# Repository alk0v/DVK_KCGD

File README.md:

This project is a replica of a color graphic display controller (KCGD) for a DVK computer, reproduced in full accordance with the schematic diagram. Unfortunately, I lost the latest version of the project in KiCAD along with the SSD disk, so the repository contains only what I managed to restore from the backup (about 50% of the finished project). However, the Gerber files were saved.
The boards have been ordered, and one board has been assembled, but unfortunately, there is no way to check its operation. The DVK computer is currently unavailable due to the war in Ukraine.

Цей проект - репліка контролера кольорового графічного дисплею (КЦГД) для комп'ютера ДВК, відтворена у повній відповідності до принципової схеми. На жаль, останню версію проекту в KiCAD я втратив разом з SSD диском, то ж в репозиторії лише те, що вдалося відновити з бекапа (десь 50% готового проекту). Але  зберіглися gerber-файли.
Плати були замовлені, одна плата зібрана, але перевірити її роботу, на жаль, нема можливості. Комп'ютер ДВК зараз недоступний через війну.

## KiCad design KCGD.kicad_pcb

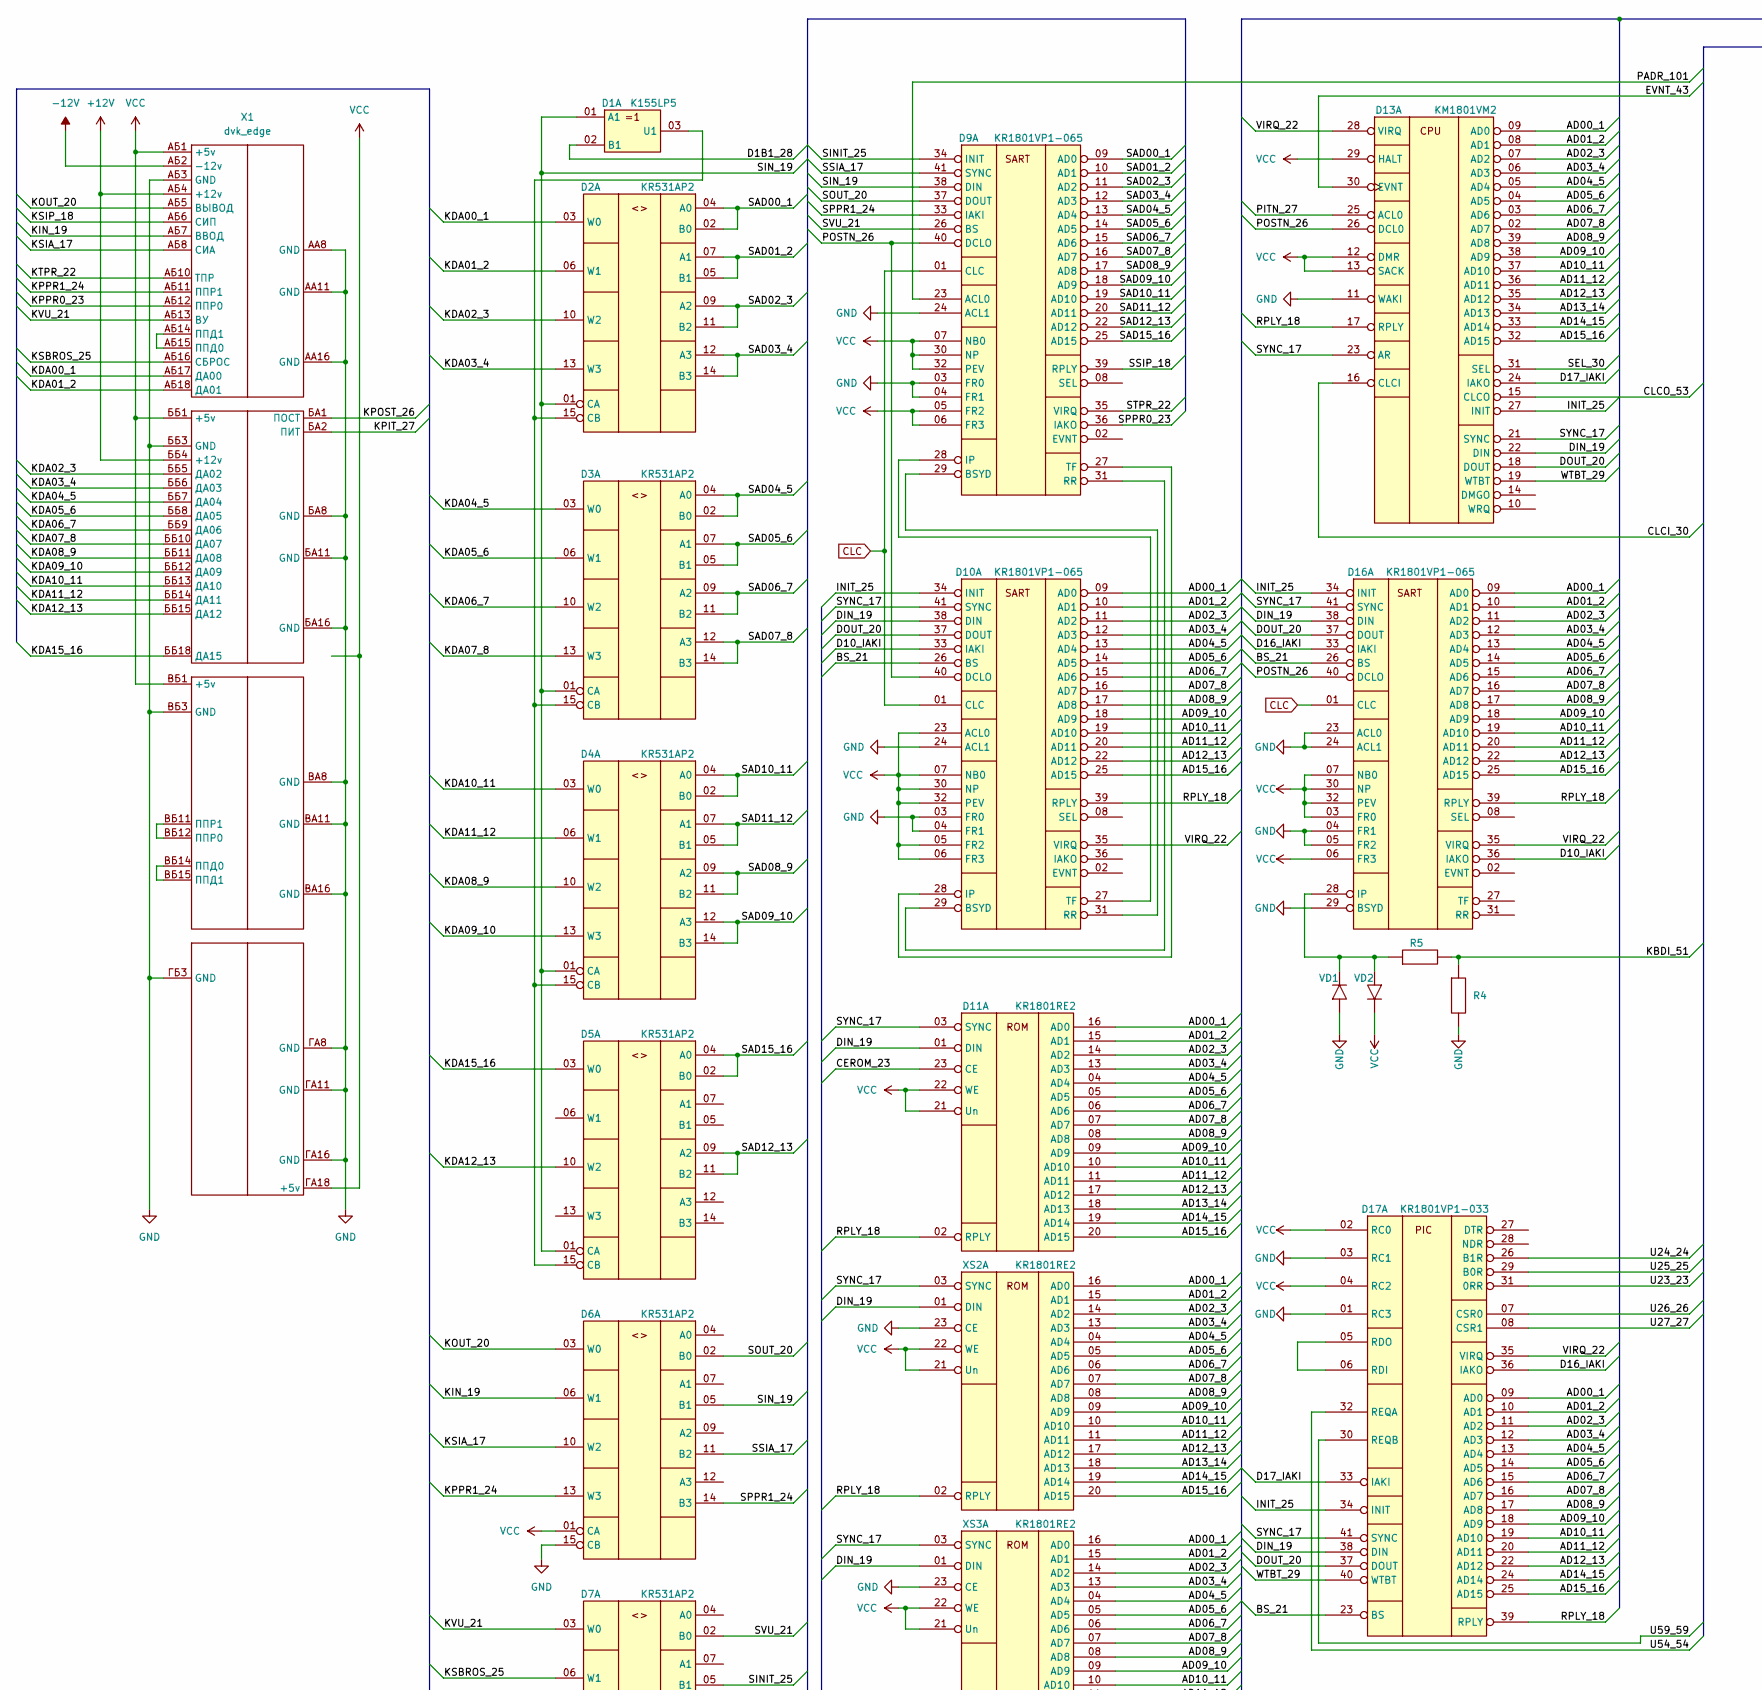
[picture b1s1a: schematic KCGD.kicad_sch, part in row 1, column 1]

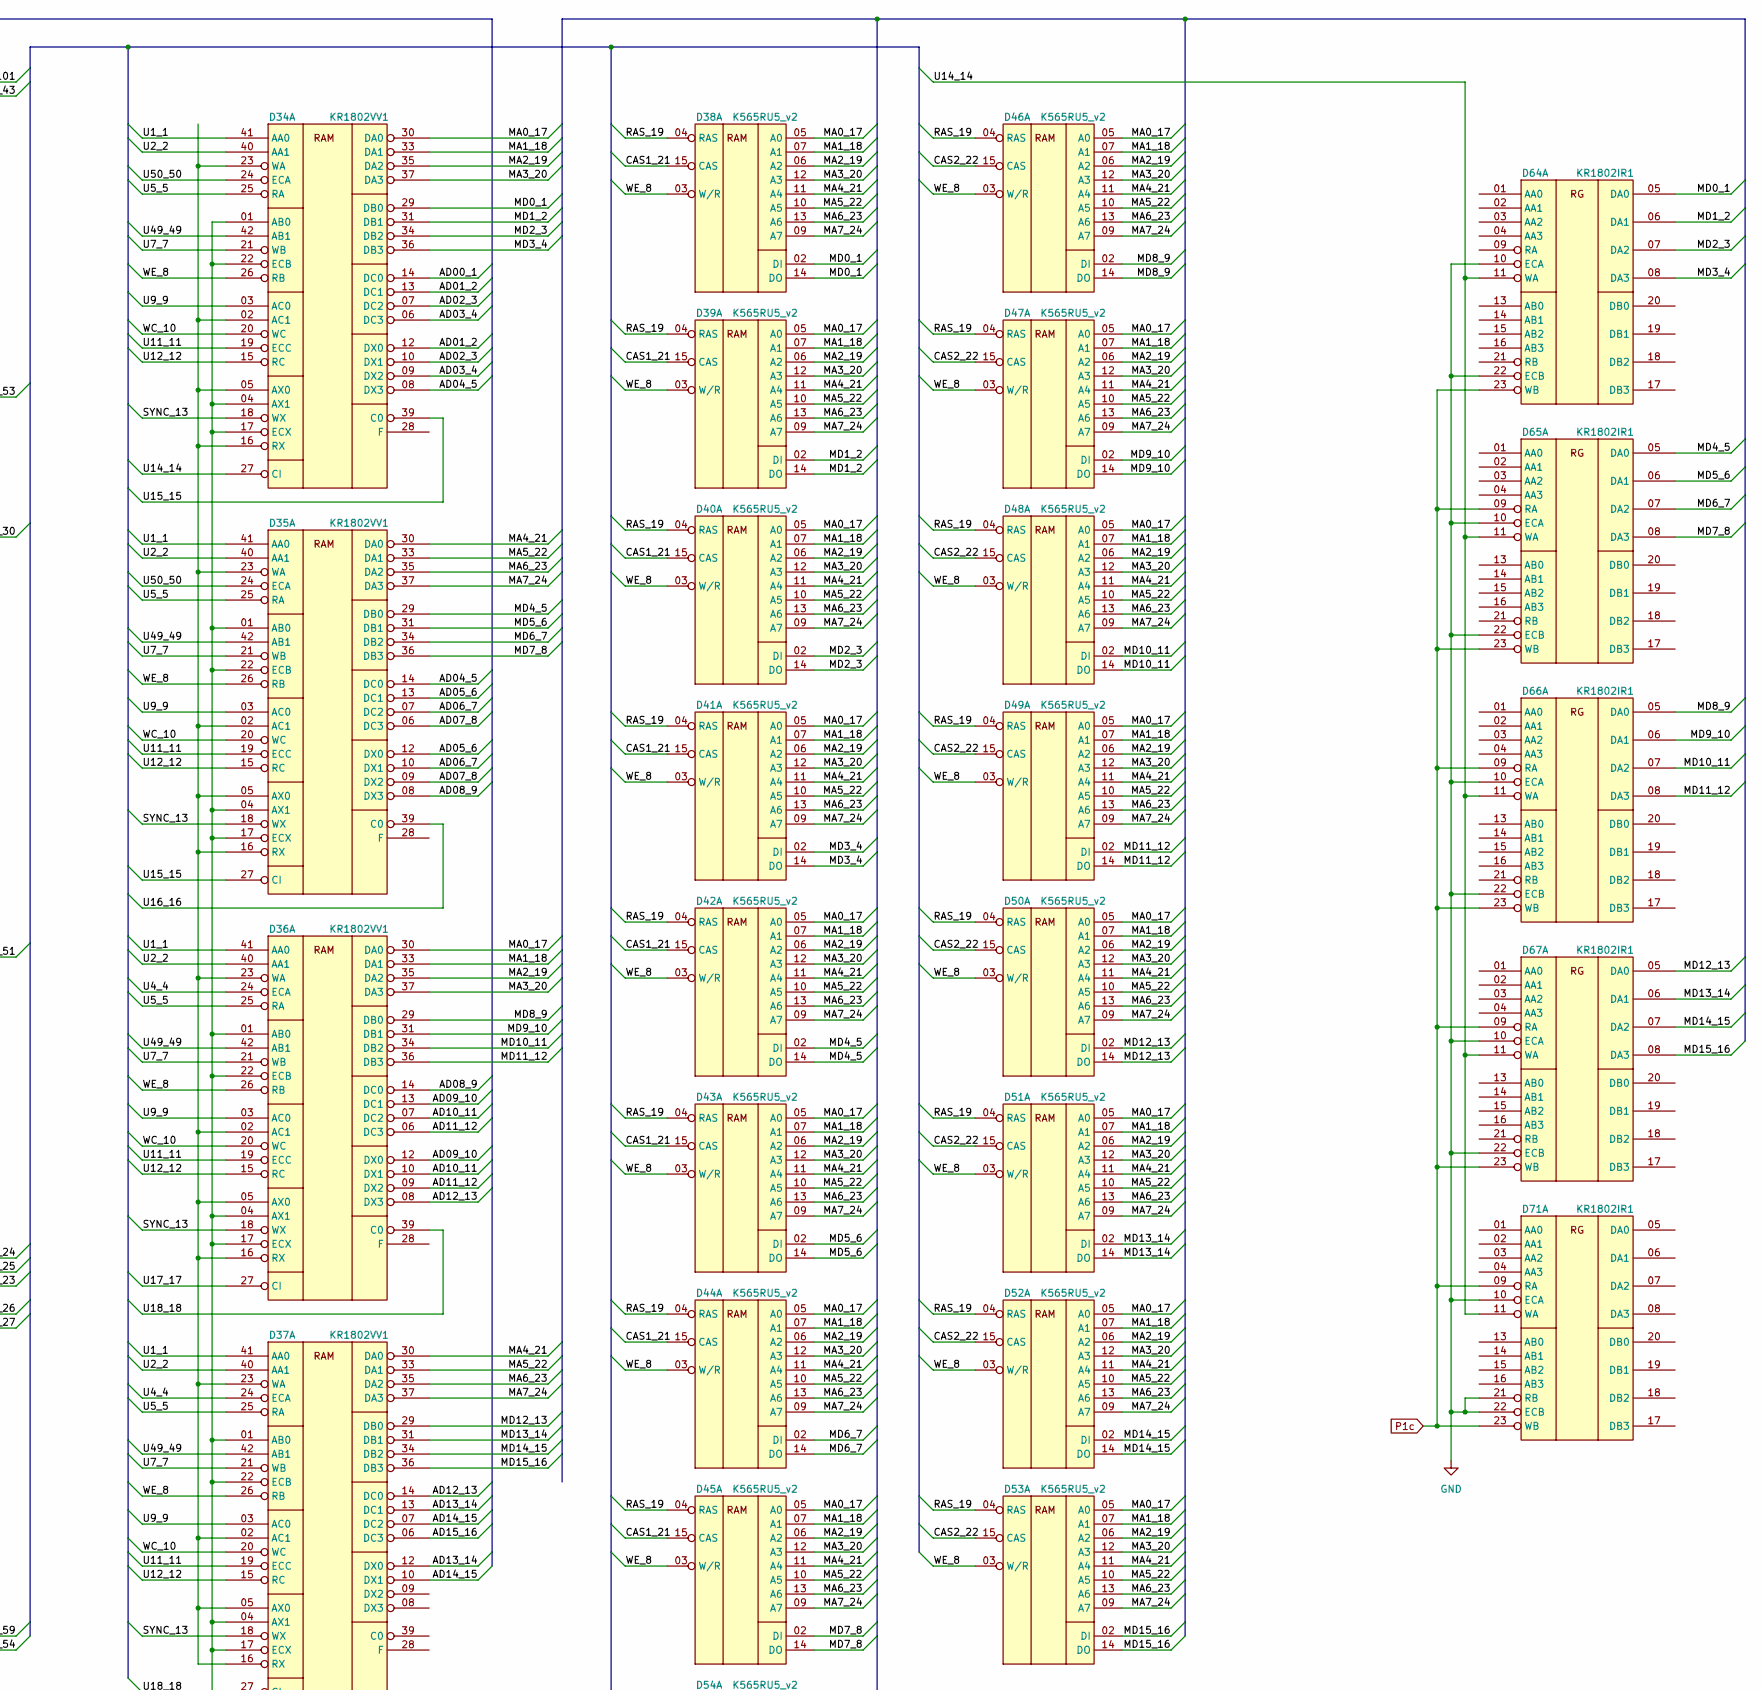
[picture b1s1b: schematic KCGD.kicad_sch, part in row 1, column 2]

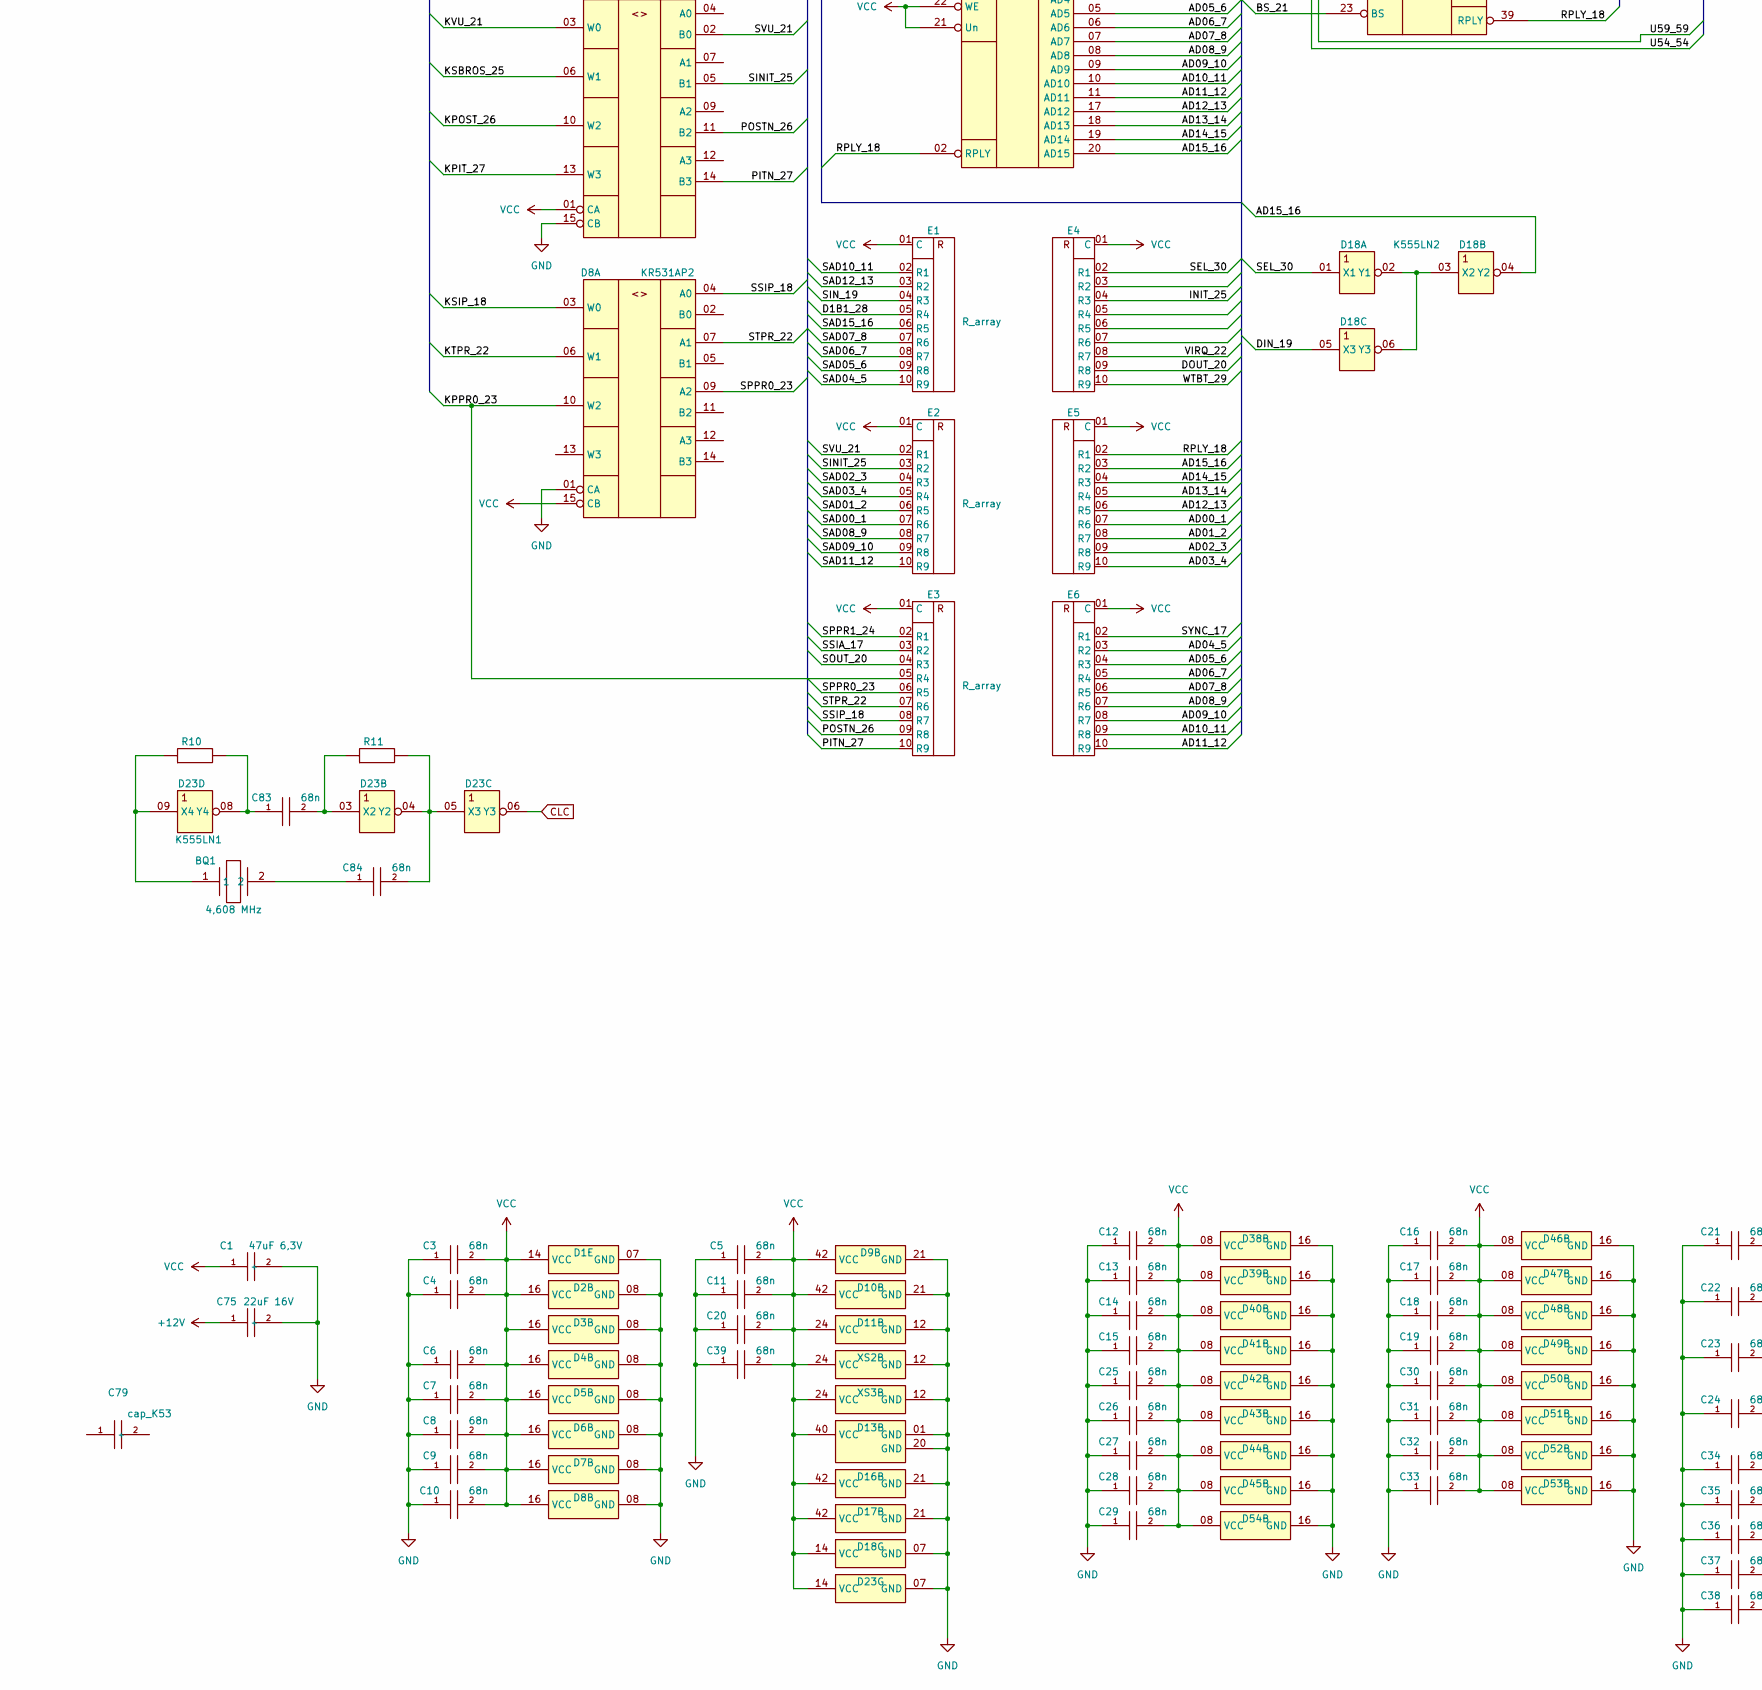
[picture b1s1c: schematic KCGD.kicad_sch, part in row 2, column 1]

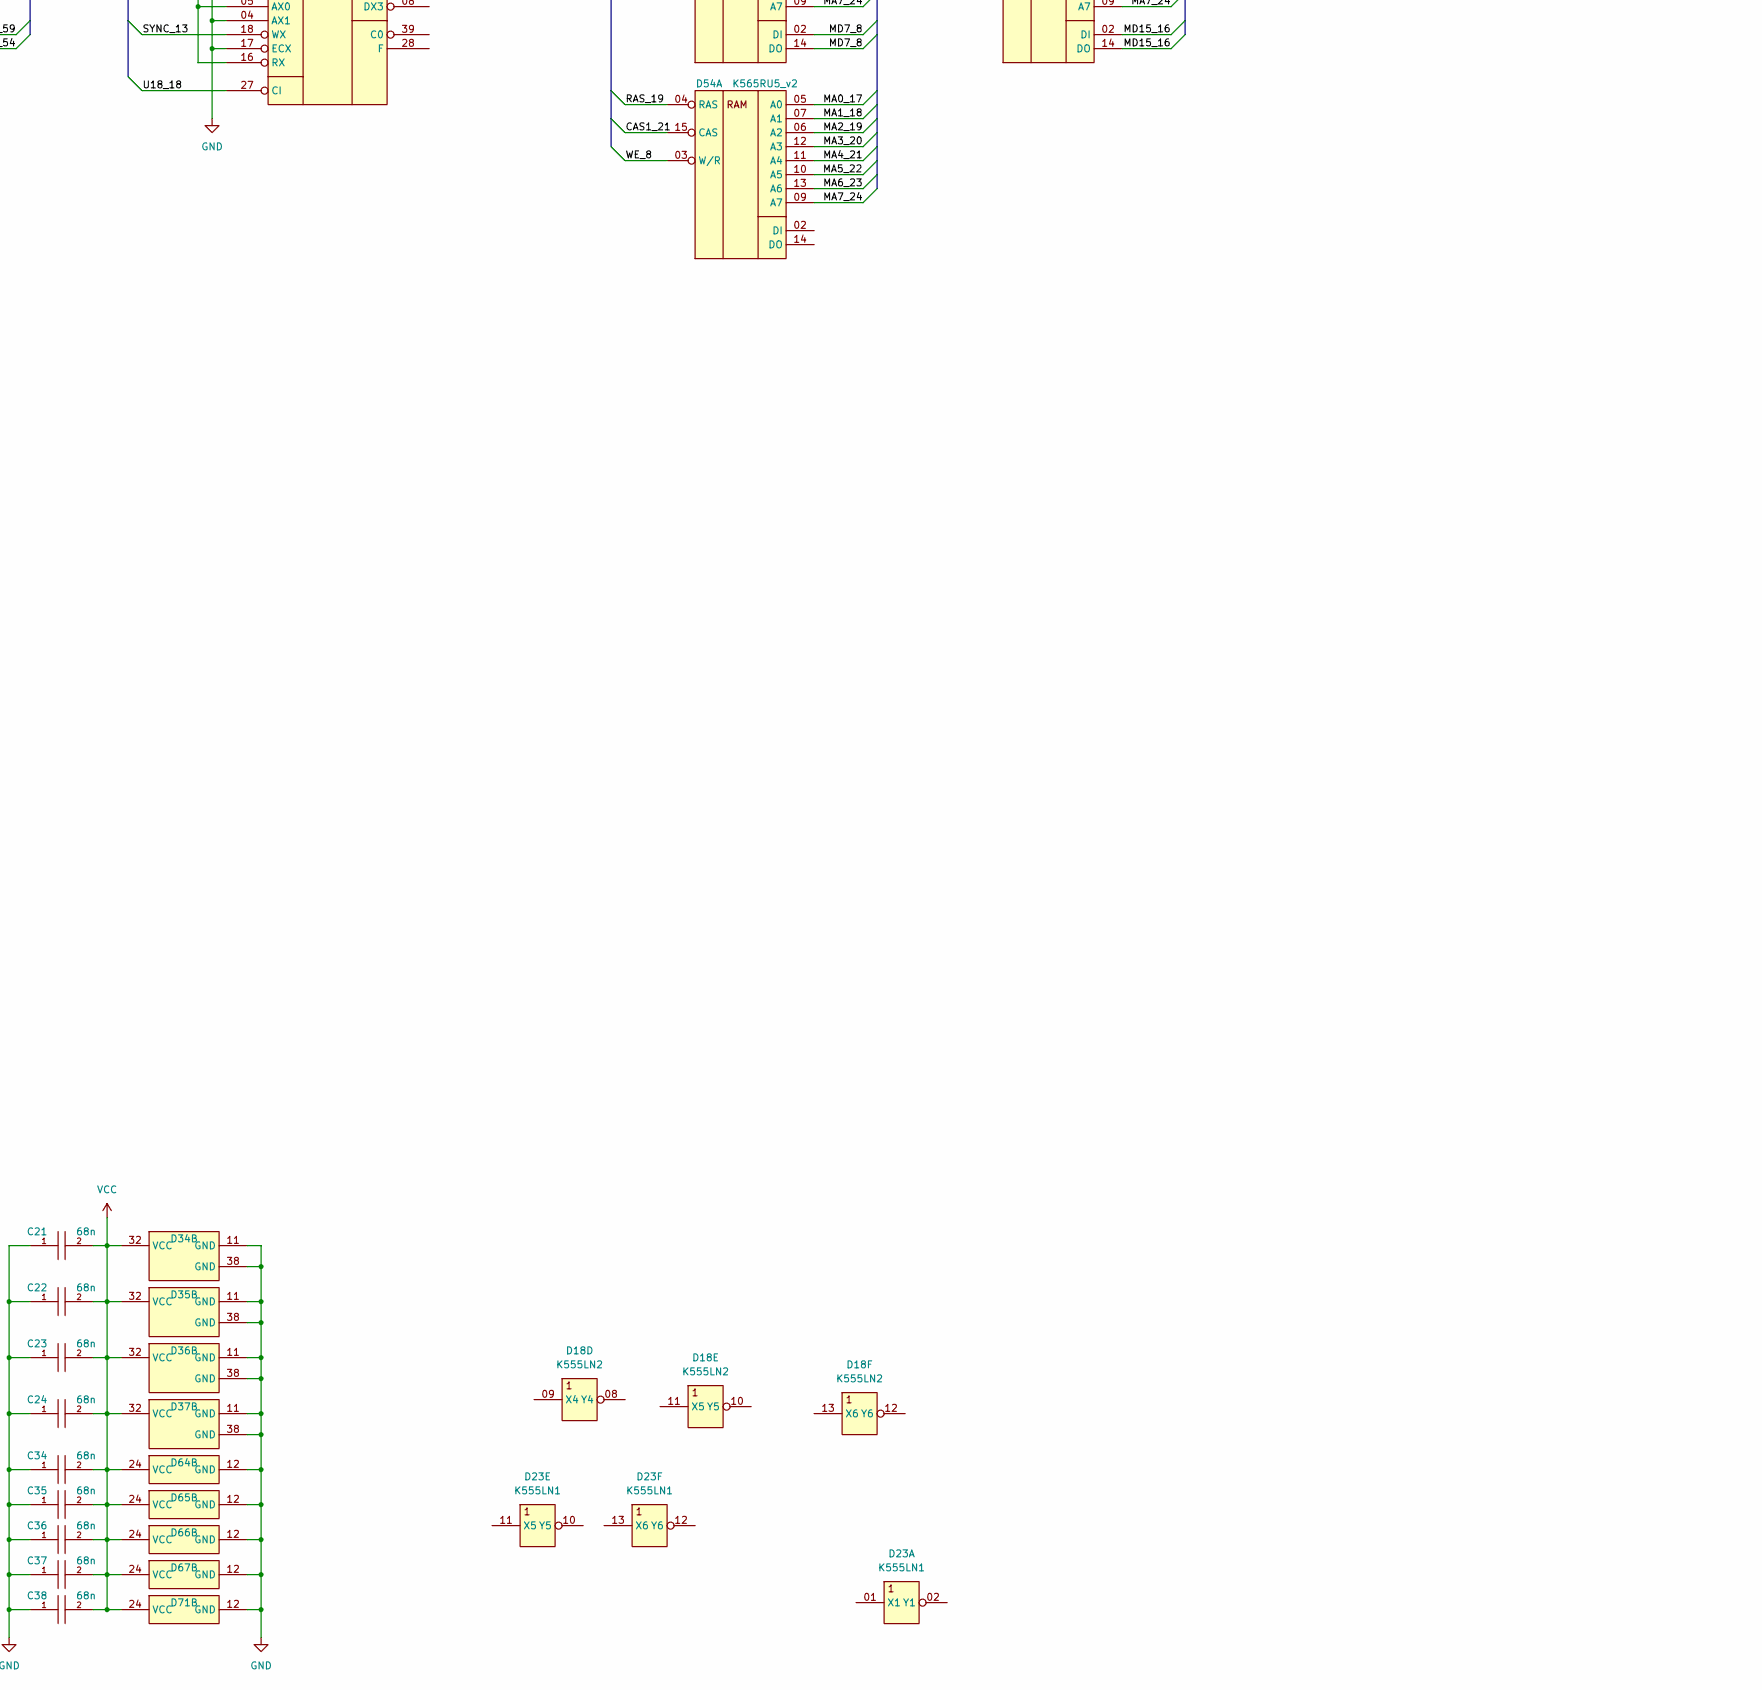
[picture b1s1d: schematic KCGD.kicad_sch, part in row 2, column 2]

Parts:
BQ1: 4,608 MHz; Quartz
C1: 47uF 6,3V; cap_K53
C3, C4, C5, C6, C7, C8, C9, C10, C11, C12, C13, C14, C15, C16, C17, C18, C19, C20, C21, C22, C23, C24, C25, C26, C27, C28, C29, C30, C31, C32, C33, C34, C35, C36, C37, C38, C39, C83, C84: 68n; cap_5mm
C75: 22uF 16V; cap_K53
C79: cap_K53
D1: K155LP5; 201.14-8
D2, D3, D4, D5, D6, D7, D8: KR531AP2; 201.16.5
D9, D10, D16: КR1801VP1-065; 429.42-5
D11: KR1801RE2; 239.24-2
D13: KM1801VM2; 2123.40-6
D17: KR1801VP1-033; 429.42-5
D18: K555LN2; 201.14-8
D23: K555LN1; 201.14-8
D34, D35, D36, D37: KR1802VV1; 429.42-5
D38, D39, D40, D41, D42, D43, D44, D45, D46, D47, D48, D49, D50, D51, D52, D53, D54: K565RU5_v2; 201.16.5
D64, D65, D66, D67, D71: KR1802IR1; 239.24-2
E1, E2, E3, E4, E5, E6: R_array; row-10
R4: 3,3k; 2pin_125
R5: 62k; 2pin_125
R10, R11: 1k; 2pin_125
VD1, VD2: VD_125; 2pin_125
X1: dvk_edge; dvk_edge_kcgd
XS2, XS3: KR1801RE2; 239.24-2

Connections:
+12V: C75.1 (+), X1.АБ4 (+12v), X1.ББ4 (+12v)
-12V: X1.АБ2 (-12v)
/AD00_1: D10.09 (AD0), D11.16 (AD0), D13.09 (AD0), D16.09 (AD0), D17.09 (AD0), D34.14 (DC0), E5.07 (R6), XS2.16 (AD0), XS3.16 (AD0)
/AD01_2: D10.10 (AD1), D11.15 (AD1), D13.08 (AD1), D16.10 (AD1), D17.10 (AD1), D34.12 (DX0), D34.13 (DC1), E5.08 (R7), XS2.15 (AD1), XS3.15 (AD1)
/AD02_3: D10.11 (AD2), D11.14 (AD2), D13.07 (AD2), D16.11 (AD2), D17.11 (AD2), D34.07 (DC2), D34.10 (DX1), E5.09 (R8), XS2.14 (AD2), XS3.14 (AD2)
/AD03_4: D10.12 (AD3), D11.13 (AD3), D13.06 (AD3), D16.12 (AD3), D17.12 (AD3), D34.06 (DC3), D34.09 (DX2), E5.10 (R9), XS2.13 (AD3), XS3.13 (AD3)
/AD04_5: D10.13 (AD4), D11.04 (AD4), D13.05 (AD4), D16.13 (AD4), D17.13 (AD4), D34.08 (DX3), D35.14 (DC0), E6.03 (R2), XS2.04 (AD4), XS3.04 (AD4)
/AD05_6: D10.14 (AD5), D11.05 (AD5), D13.04 (AD5), D16.14 (AD5), D17.14 (AD5), D35.12 (DX0), D35.13 (DC1), E6.04 (R3), XS2.05 (AD5), XS3.05 (AD5)
/AD06_7: D10.15 (AD6), D11.06 (AD6), D13.03 (AD6), D16.15 (AD6), D17.15 (AD6), D35.07 (DC2), D35.10 (DX1), E6.05 (R4), XS2.06 (AD6), XS3.06 (AD6)
/AD07_8: D10.16 (AD7), D11.07 (AD7), D13.02 (AD7), D16.16 (AD7), D17.16 (AD7), D35.06 (DC3), D35.09 (DX2), E6.06 (R5), XS2.07 (AD7), XS3.07 (AD7)
/AD08_9: D10.17 (AD8), D11.08 (AD8), D13.39 (AD8), D16.17 (AD8), D17.17 (AD8), D35.08 (DX3), D36.14 (DC0), E6.07 (R6), XS2.08 (AD8), XS3.08 (AD8)
/AD09_10: D10.18 (AD9), D11.09 (AD9), D13.38 (AD9), D16.18 (AD9), D17.18 (AD9), D36.12 (DX0), D36.13 (DC1), E6.08 (R7), XS2.09 (AD9), XS3.09 (AD9)
/AD10_11: D10.19 (AD10), D11.10 (AD10), D13.37 (AD10), D16.19 (AD10), D17.19 (AD10), D36.07 (DC2), D36.10 (DX1), E6.09 (R8), XS2.10 (AD10), XS3.10 (AD10)
/AD11_12: D10.20 (AD11), D11.11 (AD11), D13.36 (AD11), D16.20 (AD11), D17.20 (AD11), D36.06 (DC3), D36.09 (DX2), E6.10 (R9), XS2.11 (AD11), XS3.11 (AD11)
/AD12_13: D10.22 (AD12), D11.17 (AD12), D13.35 (AD12), D16.22 (AD12), D17.22 (AD12), D36.08 (DX3), D37.14 (DC0), E5.06 (R5), XS2.17 (AD12), XS3.17 (AD12)
/AD13_14: D11.18 (AD13), D13.34 (AD13), D37.12 (DX0), D37.13 (DC1), E5.05 (R4), XS2.18 (AD13), XS3.18 (AD13)
/AD14_15: D11.19 (AD14), D13.33 (AD14), D17.24 (AD14), D37.07 (DC2), D37.10 (DX1), E5.04 (R3), XS2.19 (AD14), XS3.19 (AD14)
/AD15_16: D11.20 (AD15), D13.32 (AD15), D16.25 (AD15), D17.25 (AD15), D18.04 (Y2), D37.06 (DC3), E5.03 (R2), XS2.20 (AD15), XS3.20 (AD15)
/BS_21: D10.26 (BS), D16.26 (BS), D17.23 (BS)
/CAS1_21: D38.15 (CAS), D39.15 (CAS), D40.15 (CAS), D41.15 (CAS), D42.15 (CAS), D43.15 (CAS), D44.15 (CAS), D45.15 (CAS), D54.15 (CAS)
/CAS2_22: D46.15 (CAS), D47.15 (CAS), D48.15 (CAS), D49.15 (CAS), D50.15 (CAS), D51.15 (CAS), D52.15 (CAS), D53.15 (CAS)
/CEROM_23: D11.23 (CE)
/CLCI_30: D13.16 (CLCI)
/CLCO_53: D13.15 (CLCO)
/D1B1_28: D1.02 (B1), E1.05 (R4)
/D10_IAKI: D10.33 (IAKI), D16.36 (IAKO)
/D16_IAKI: D16.33 (IAKI), D17.36 (IAKO)
/D17_IAKI: D13.24 (IAKO), D17.33 (IAKI)
/DIN_19: D10.38 (DIN), D11.01 (DIN), D13.22 (DIN), D16.38 (DIN), D17.38 (DIN), D18.05 (X3), XS2.01 (DIN), XS3.01 (DIN)
/DOUT_20: D10.37 (DOUT), D13.18 (DOUT), D16.37 (DOUT), D17.37 (DOUT), E4.09 (R8)
/EVNT_43: D13.30 (EVNT)
/INIT_25: D10.34 (INIT), D13.27 (INIT), D16.34 (INIT), D17.34 (INIT), E4.04 (R3)
/KBDI_51: R4.1, R5.2
/KDA00_1: D2.03 (W0), X1.АБ17 (ДА00)
/KDA01_2: D2.06 (W1), X1.АБ18 (ДА01)
/KDA02_3: D2.10 (W2), X1.ББ5 (ДА02)
/KDA03_4: D2.13 (W3), X1.ББ6 (ДА03)
/KDA04_5: D3.03 (W0), X1.ББ7 (ДА04)
/KDA05_6: D3.06 (W1), X1.ББ8 (ДА05)
/KDA06_7: D3.10 (W2), X1.ББ9 (ДА06)
/KDA07_8: D3.13 (W3), X1.ББ10 (ДА07)
/KDA08_9: D4.10 (W2), X1.ББ11 (ДА08)
/KDA09_10: D4.13 (W3), X1.ББ12 (ДА09)
/KDA10_11: D4.03 (W0), X1.ББ13 (ДА10)
/KDA11_12: D4.06 (W1), X1.ББ14 (ДА11)
/KDA12_13: D5.10 (W2), X1.ББ15 (ДА12)
/KDA15_16: D5.03 (W0), X1.ББ18 (ДА15)
/KIN_19: D6.06 (W1), X1.АБ7 (ВВОД)
/KOUT_20: D6.03 (W0), X1.АБ5 (ВЫВОД)
/KPIT_27: D7.13 (W3), X1.БА2 (ПИТ)
/KPOST_26: D7.10 (W2), X1.БА1 (ПОСТ)
/KPPR0_23: D8.10 (W2), E3.05 (R4), X1.АБ12 (ППР0)
/KPPR1_24: D6.13 (W3), X1.АБ11 (ППР1)
/KSBROS_25: D7.06 (W1), X1.АБ16 (СБРОС)
/KSIA_17: D6.10 (W2), X1.АБ8 (СИА)
/KSIP_18: D8.03 (W0), X1.АБ6 (СИП)
/KTPR_22: D8.06 (W1), X1.АБ10 (ТПР)
/KVU_21: D7.03 (W0), X1.АБ13 (ВУ)
/MA0_17: D34.30 (DA0), D36.30 (DA0), D38.05 (A0), D39.05 (A0), D40.05 (A0), D41.05 (A0), D42.05 (A0), D43.05 (A0), D44.05 (A0), D45.05 (A0), D46.05 (A0), D47.05 (A0), D48.05 (A0), D49.05 (A0), D50.05 (A0), D51.05 (A0), D52.05 (A0), D53.05 (A0), D54.05 (A0)
/MA1_18: D34.33 (DA1), D36.33 (DA1), D38.07 (A1), D39.07 (A1), D40.07 (A1), D41.07 (A1), D42.07 (A1), D43.07 (A1), D44.07 (A1), D45.07 (A1), D46.07 (A1), D47.07 (A1), D48.07 (A1), D49.07 (A1), D50.07 (A1), D51.07 (A1), D52.07 (A1), D53.07 (A1), D54.07 (A1)
/MA2_19: D34.35 (DA2), D36.35 (DA2), D38.06 (A2), D39.06 (A2), D40.06 (A2), D41.06 (A2), D42.06 (A2), D43.06 (A2), D44.06 (A2), D45.06 (A2), D46.06 (A2), D47.06 (A2), D48.06 (A2), D49.06 (A2), D50.06 (A2), D51.06 (A2), D52.06 (A2), D53.06 (A2), D54.06 (A2)
/MA3_20: D34.37 (DA3), D36.37 (DA3), D38.12 (A3), D39.12 (A3), D40.12 (A3), D41.12 (A3), D42.12 (A3), D43.12 (A3), D44.12 (A3), D45.12 (A3), D46.12 (A3), D47.12 (A3), D48.12 (A3), D49.12 (A3), D50.12 (A3), D51.12 (A3), D52.12 (A3), D53.12 (A3), D54.12 (A3)
/MA4_21: D35.30 (DA0), D37.30 (DA0), D38.11 (A4), D39.11 (A4), D40.11 (A4), D41.11 (A4), D42.11 (A4), D43.11 (A4), D44.11 (A4), D45.11 (A4), D46.11 (A4), D47.11 (A4), D48.11 (A4), D49.11 (A4), D50.11 (A4), D51.11 (A4), D52.11 (A4), D53.11 (A4), D54.11 (A4)
/MA5_22: D35.33 (DA1), D37.33 (DA1), D38.10 (A5), D39.10 (A5), D40.10 (A5), D41.10 (A5), D42.10 (A5), D43.10 (A5), D44.10 (A5), D45.10 (A5), D46.10 (A5), D47.10 (A5), D48.10 (A5), D49.10 (A5), D50.10 (A5), D51.10 (A5), D52.10 (A5), D53.10 (A5), D54.10 (A5)
/MA6_23: D35.35 (DA2), D37.35 (DA2), D38.13 (A6), D39.13 (A6), D40.13 (A6), D41.13 (A6), D42.13 (A6), D43.13 (A6), D44.13 (A6), D45.13 (A6), D46.13 (A6), D47.13 (A6), D48.13 (A6), D49.13 (A6), D50.13 (A6), D51.13 (A6), D52.13 (A6), D53.13 (A6), D54.13 (A6)
/MA7_24: D35.37 (DA3), D37.37 (DA3), D38.09 (A7), D39.09 (A7), D40.09 (A7), D41.09 (A7), D42.09 (A7), D43.09 (A7), D44.09 (A7), D45.09 (A7), D46.09 (A7), D47.09 (A7), D48.09 (A7), D49.09 (A7), D50.09 (A7), D51.09 (A7), D52.09 (A7), D53.09 (A7), D54.09 (A7)
/MD0_1: D34.29 (DB0), D38.02 (DI), D38.14 (DO), D64.05 (DA0)
/MD1_2: D34.31 (DB1), D39.02 (DI), D39.14 (DO), D64.06 (DA1)
/MD2_3: D34.34 (DB2), D40.02 (DI), D40.14 (DO), D64.07 (DA2)
/MD3_4: D34.36 (DB3), D41.02 (DI), D41.14 (DO), D64.08 (DA3)
/MD4_5: D35.29 (DB0), D42.02 (DI), D42.14 (DO), D65.05 (DA0)
/MD5_6: D35.31 (DB1), D43.02 (DI), D43.14 (DO), D65.06 (DA1)
/MD6_7: D35.34 (DB2), D44.02 (DI), D44.14 (DO), D65.07 (DA2)
/MD7_8: D35.36 (DB3), D45.02 (DI), D45.14 (DO), D65.08 (DA3)
/MD8_9: D36.29 (DB0), D46.02 (DI), D46.14 (DO), D66.05 (DA0)
/MD9_10: D36.31 (DB1), D47.02 (DI), D47.14 (DO), D66.06 (DA1)
/MD10_11: D36.34 (DB2), D48.02 (DI), D48.14 (DO), D66.07 (DA2)
/MD11_12: D36.36 (DB3), D49.02 (DI), D49.14 (DO), D66.08 (DA3)
/MD12_13: D37.29 (DB0), D50.02 (DI), D50.14 (DO), D67.05 (DA0)
/MD13_14: D37.31 (DB1), D51.02 (DI), D51.14 (DO), D67.06 (DA1)
/MD14_15: D37.34 (DB2), D52.02 (DI), D52.14 (DO), D67.07 (DA2)
/MD15_16: D37.36 (DB3), D53.02 (DI), D53.14 (DO), D67.08 (DA3)
/PADR_101: D9.23 (ACL0)
/PITN_27: D7.14 (B3), D13.25 (ACL0), E3.10 (R9)
/POSTN_26: D7.11 (B2), D9.40 (DCLO), D10.40 (DCLO), D13.26 (DCL0), D16.40 (DCLO), E3.09 (R8)
/RAS_19: D38.04 (RAS), D39.04 (RAS), D40.04 (RAS), D41.04 (RAS), D42.04 (RAS), D43.04 (RAS), D44.04 (RAS), D45.04 (RAS), D46.04 (RAS), D47.04 (RAS), D48.04 (RAS), D49.04 (RAS), D50.04 (RAS), D51.04 (RAS), D52.04 (RAS), D53.04 (RAS), D54.04 (RAS)
/RPLY_18: D10.39 (RPLY), D11.02 (RPLY), D13.17 (RPLY), D16.39 (RPLY), D17.39 (RPLY), E5.02 (R1), XS2.02 (RPLY), XS3.02 (RPLY)
/SAD00_1: D2.02 (B0), D2.04 (A0), D9.09 (AD0), E2.07 (R6)
/SAD01_2: D2.05 (B1), D2.07 (A1), D9.10 (AD1), E2.06 (R5)
/SAD02_3: D2.09 (A2), D2.11 (B2), D9.11 (AD2), E2.04 (R3)
/SAD03_4: D2.12 (A3), D2.14 (B3), D9.12 (AD3), E2.05 (R4)
/SAD04_5: D3.02 (B0), D3.04 (A0), D9.13 (AD4), E1.10 (R9)
/SAD05_6: D3.05 (B1), D3.07 (A1), D9.14 (AD5), E1.09 (R8)
/SAD06_7: D3.09 (A2), D3.11 (B2), D9.15 (AD6), E1.08 (R7)
/SAD07_8: D3.12 (A3), D3.14 (B3), D9.16 (AD7), E1.07 (R6)
/SAD08_9: D4.09 (A2), D4.11 (B2), D9.17 (AD8), E2.08 (R7)
/SAD09_10: D4.12 (A3), D4.14 (B3), D9.18 (AD9), E2.09 (R8)
/SAD10_11: D4.02 (B0), D4.04 (A0), D9.19 (AD10), E1.02 (R1)
/SAD11_12: D4.05 (B1), D4.07 (A1), D9.20 (AD11), E2.10 (R9)
/SAD12_13: D5.09 (A2), D5.11 (B2), D9.22 (AD12), E1.03 (R2)
/SAD15_16: D5.02 (B0), D5.04 (A0), D9.25 (AD15), E1.06 (R5)
/SEL_30: D13.31 (SEL), D18.01 (X1), E4.02 (R1)
/SINIT_25: D7.05 (B1), D9.34 (INIT), E2.03 (R2)
/SIN_19: D1.01 (A1), D2.01 (CA), D3.01 (CA), D4.01 (CA), D5.01 (CA), D6.05 (B1), D9.38 (DIN), E1.04 (R3)
/SOUT_20: D6.02 (B0), D9.37 (DOUT), E3.04 (R3)
/SPPR0_23: D8.09 (A2), D9.36 (IAKO), E3.06 (R5)
/SPPR1_24: D6.14 (B3), D9.33 (IAKI), E3.02 (R1)
/SSIA_17: D6.11 (B2), D9.41 (SYNC), E3.03 (R2)
/SSIP_18: D8.04 (A0), D9.39 (RPLY), E3.08 (R7)
/STPR_22: D8.07 (A1), D9.35 (VIRQ), E3.07 (R6)
/SVU_21: D7.02 (B0), D9.26 (BS), E2.02 (R1)
/SYNC_13: D34.18 (WX), D35.18 (WX), D36.18 (WX), D37.18 (WX)
/SYNC_17: D10.41 (SYNC), D11.03 (SYNC), D13.21 (SYNC), D13.23 (AR), D16.41 (SYNC), D17.41 (SYNC), E6.02 (R1), XS2.03 (SYNC), XS3.03 (SYNC)
/U1_1: D34.41 (AA0), D35.41 (AA0), D36.41 (AA0), D37.41 (AA0)
/U2_2: D34.40 (AA1), D35.40 (AA1), D36.40 (AA1), D37.40 (AA1)
/U4_4: D36.24 (ECA), D37.24 (ECA)
/U5_5: D34.25 (RA), D35.25 (RA), D36.25 (RA), D37.25 (RA)
/U7_7: D34.21 (WB), D35.21 (WB), D36.21 (WB), D37.21 (WB)
/U9_9: D34.03 (AC0), D35.03 (AC0), D36.03 (AC0), D37.03 (AC0)
/U11_11: D34.19 (ECC), D35.19 (ECC), D36.19 (ECC), D37.19 (ECC)
/U12_12: D34.15 (RC), D35.15 (RC), D36.15 (RC), D37.15 (RC)
/U14_14: D34.27 (CI), D64.11 (WA), D65.11 (WA), D66.11 (WA), D67.11 (WA), D71.11 (WA)
/U15_15: D34.39 (C0), D35.27 (CI)
/U16_16: D35.39 (C0)
/U17_17: D36.27 (CI)
/U18_18: D36.39 (C0), D37.27 (CI)
/U23_23: D17.31 (0RR)
/U24_24: D17.26 (B1R)
/U25_25: D17.29 (B0R)
/U26_26: D17.07 (CSR0)
/U27_27: D17.08 (CSR1)
/U49_49: D34.42 (AB1), D35.42 (AB1), D36.42 (AB1), D37.42 (AB1)
/U50_50: D34.24 (ECA), D35.24 (ECA)
/U54_54: D17.32 (REQA)
/U59_59: D17.30 (REQB)
/VIRQ_22: D10.35 (VIRQ), D13.28 (VIRQ), D16.35 (VIRQ), D17.35 (VIRQ), E4.08 (R7)
/WC_10: D34.20 (WC), D35.20 (WC), D36.20 (WC), D37.20 (WC)
/WE_8: D34.26 (RB), D35.26 (RB), D36.26 (RB), D37.26 (RB), D38.03 (W/R), D39.03 (W/R), D40.03 (W/R), D41.03 (W/R), D42.03 (W/R), D43.03 (W/R), D44.03 (W/R), D45.03 (W/R), D46.03 (W/R), D47.03 (W/R), D48.03 (W/R), D49.03 (W/R), D50.03 (W/R), D51.03 (W/R), D52.03 (W/R), D53.03 (W/R), D54.03 (W/R)
/WTBT_29: D13.19 (WTBT), D17.40 (WTBT), E4.10 (R9)
CLC: D9.01 (CLC), D10.01 (CLC), D16.01 (CLC), D23.06 (Y3)
GND: C1.2, C3.1, C4.1, C5.1, C6.1, C7.1, C8.1, C9.1, C10.1, C11.1, C12.1, C13.1, C14.1, C15.1, C16.1, C17.1, C18.1, C19.1, C20.1, C21.1, C22.1, C23.1, C24.1, C25.1, C26.1, C27.1, C28.1, C29.1, C30.1, C31.1, C32.1, C33.1, C34.1, C35.1, C36.1, C37.1, C38.1, C39.1, C75.2, D1.07 (GND), D2.08 (GND), D3.08 (GND), D4.08 (GND), D5.08 (GND), D6.08 (GND), D6.15 (CB), D7.08 (GND), D7.15 (CB), D8.01 (CA), D8.08 (GND), D9.03 (FR0), D9.04 (FR1), D9.21 (GND), D9.24 (ACL1), D10.03 (FR0), D10.04 (FR1), D10.21 (GND), D10.24 (ACL1), D11.12 (GND), D13.01 (GND), D13.11 (WAKI), D13.20 (GND), D16.04 (FR1), D16.05 (FR2), D16.21 (GND), D16.23 (ACL0), D16.24 (ACL1), D16.29 (BSYD), D17.01 (RC3), D17.03 (RC1), D17.21 (GND), D18.07 (GND), D23.07 (GND), D34.01 (AB0), D34.04 (AX1), D34.11 (GND), D34.17 (ECX), D34.22 (ECB), D34.38 (GND), D35.01 (AB0), D35.04 (AX1), D35.11 (GND), D35.17 (ECX), D35.22 (ECB), D35.38 (GND), D36.01 (AB0), D36.04 (AX1), D36.11 (GND), D36.17 (ECX), D36.22 (ECB), D36.38 (GND), D37.01 (AB0), D37.04 (AX1), D37.11 (GND), D37.17 (ECX), D37.22 (ECB), D37.38 (GND), D38.16 (GND), D39.16 (GND), D40.16 (GND), D41.16 (GND), D42.16 (GND), D43.16 (GND), D44.16 (GND), D45.16 (GND), D46.16 (GND), D47.16 (GND), D48.16 (GND), D49.16 (GND), D50.16 (GND), D51.16 (GND), D52.16 (GND), D53.16 (GND), D54.16 (GND), D64.10 (ECA), D64.12 (GND), D64.22 (ECB), D65.10 (ECA), D65.12 (GND), D65.22 (ECB), D66.10 (ECA), D66.12 (GND), D66.22 (ECB), D67.10 (ECA), D67.12 (GND), D67.22 (ECB), D71.10 (ECA), D71.12 (GND), D71.21 (RB), D71.22 (ECB), R4.2, VD1.1, X1.АА8 (GND), X1.АА11 (GND), X1.АА16 (GND), X1.АБ3 (GND), X1.БА8 (GND), X1.БА11 (GND), X1.БА16 (GND), X1.ББ3 (GND), X1.ВА8 (GND), X1.ВА11 (GND), X1.ВА16 (GND), X1.ВБ3 (GND), X1.ГА8 (GND), X1.ГА11 (GND), X1.ГА16 (GND), X1.ГБ3 (GND), XS2.12 (GND), XS2.23 (CE), XS3.12 (GND), XS3.23 (CE)
unnamed: BQ1.1, D23.09 (X4), R10.1
unnamed: BQ1.2, C84.1
unnamed: C83.1, D23.08 (Y4), R10.2
unnamed: C83.2, D23.03 (X2), R11.1
unnamed: D1.03 (U1), D2.15 (CB), D3.15 (CB), D4.15 (CB), D5.15 (CB)
unnamed: D9.28 (IP), D10.27 (TF)
unnamed: D9.27 (TF), D10.28 (IP)
unnamed: D9.31 (RR), D10.29 (BSYD)
unnamed: D9.29 (BSYD), D10.31 (RR)
unnamed: D16.28 (IP), R5.1, VD1.2, VD2.1
unnamed: D17.05 (RDO), D17.06 (RDI)
unnamed: D18.02 (Y1), D18.03 (X2), D18.06 (Y3)
unnamed: C84.2, D23.04 (Y2), D23.05 (X3), R11.2
unnamed: D34.02 (AC1), D34.05 (AX0), D34.16 (RX), D34.23 (WA), D35.02 (AC1), D35.05 (AX0), D35.16 (RX), D35.23 (WA), D36.02 (AC1), D36.05 (AX0), D36.16 (RX), D36.23 (WA), D37.02 (AC1), D37.05 (AX0), D37.16 (RX), D37.23 (WA)
unnamed: X1.АБ14 (ППД1), X1.АБ15 (ППД0)
unnamed: X1.ВБ11 (ППР1), X1.ВБ12 (ППР0)
unnamed: X1.ВБ14 (ППД0), X1.ВБ15 (ППД1)
P1c: D64.23 (WB), D65.09 (RA), D65.23 (WB), D66.09 (RA), D66.23 (WB), D67.09 (RA), D67.23 (WB), D71.09 (RA), D71.23 (WB)
VCC: C1.1 (+), C3.2, C4.2, C5.2, C6.2, C7.2, C8.2, C9.2, C10.2, C11.2, C12.2, C13.2, C14.2, C15.2, C16.2, C17.2, C18.2, C19.2, C20.2, C21.2, C22.2, C23.2, C24.2, C25.2, C26.2, C27.2, C28.2, C29.2, C30.2, C31.2, C32.2, C33.2, C34.2, C35.2, C36.2, C37.2, C38.2, C39.2, D1.14 (VCC), D2.16 (VCC), D3.16 (VCC), D4.16 (VCC), D5.16 (VCC), D6.01 (CA), D6.16 (VCC), D7.01 (CA), D7.16 (VCC), D8.15 (CB), D8.16 (VCC), D9.05 (FR2), D9.06 (FR3), D9.07 (NB0), D9.30 (NP), D9.32 (PEV), D9.42 (VCC), D10.05 (FR2), D10.06 (FR3), D10.07 (NB0), D10.23 (ACL0), D10.30 (NP), D10.32 (PEV), D10.42 (VCC), D11.21 (Un), D11.22 (WE), D11.24 (VCC), D13.12 (DMR), D13.13 (SACK), D13.29 (HALT), D13.40 (VCC), D16.03 (FR0), D16.06 (FR3), D16.07 (NB0), D16.30 (NP), D16.32 (PEV), D16.42 (VCC), D17.02 (RC0), D17.04 (RC2), D17.42 (VCC), D18.14 (VCC), D23.14 (VCC), D34.32 (VCC), D35.32 (VCC), D36.32 (VCC), D37.32 (VCC), D38.08 (VCC), D39.08 (VCC), D40.08 (VCC), D41.08 (VCC), D42.08 (VCC), D43.08 (VCC), D44.08 (VCC), D45.08 (VCC), D46.08 (VCC), D47.08 (VCC), D48.08 (VCC), D49.08 (VCC), D50.08 (VCC), D51.08 (VCC), D52.08 (VCC), D53.08 (VCC), D54.08 (VCC), D64.24 (VCC), D65.24 (VCC), D66.24 (VCC), D67.24 (VCC), D71.24 (VCC), E1.01 (C), E2.01 (C), E3.01 (C), E4.01 (C), E5.01 (C), E6.01 (C), VD2.2, X1.АБ1 (+5v), X1.ББ1 (+5v), X1.ВБ1 (+5v), X1.ГА18 (+5v), XS2.21 (Un), XS2.22 (WE), XS2.24 (VCC), XS3.21 (Un), XS3.22 (WE), XS3.24 (VCC)

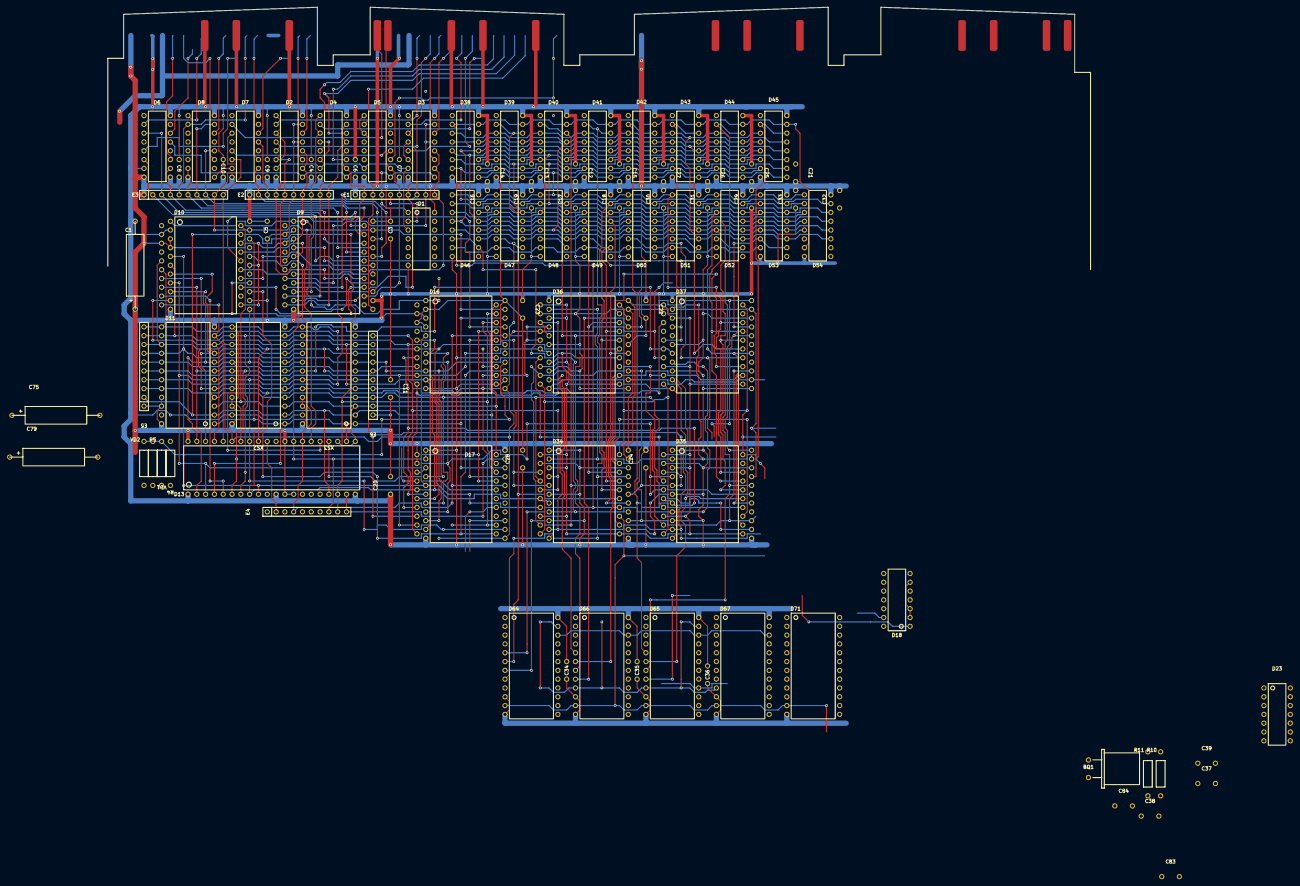
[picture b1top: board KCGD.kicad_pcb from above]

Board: 2 copper layers, 100 parts (0 on the bottom side), 145 nets.
